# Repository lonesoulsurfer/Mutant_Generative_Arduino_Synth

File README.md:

# Mutant_Generative_Arduino_Synth

UPDATE: I have updated the Mutant code so it can be loaded using the most recent Mozzi Library.  You can find the code in the 'Mutant_Updated' file.  It works perfectly and there is no changes to the sounds etc.

 Meebleeps awesome Mutant Synth in modular format

First and foremost - I need to do a huge shoutout to MeeBleeps (https://github.com/Meebleeps/MeeBleeps-Mutant-Synth) who designed this amazing synth. I've designed a PCB and front panel to fit modular synths or you could use it as a stand alone synth if you wanted to.  You can power the synth used a voltage range from 9 to 12V's

You can find a step by step guide on my Instructables page on how to build your own - https://www.instructables.com/Mutant-Generative-Arduino-Synth/

I have also posted a video on my YouTube page - https://www.youtube.com/watch?v=L1Gzkz4_xpQ

The main goal with building this module is to create my own 'simple to build' modular synth. I wanted to keep everything as easy as possble with each module built with the following aims:

Can be powered by 9V (and 12V)
Easy to build with minimum components
Use Arduino to keep it simple (plus it helps to keep the components down and everything in tune)
Can fit into any modular synth Eurorck (include the ability to power the module via normal module power sources)
Has to sound great!
Lastly, it should be portable and be powered from a 9V battery

So what is the Mutant Synth? Well it's a generative synth based around a Arduino Nano and a handful of other components and produces a rich soundscape of sounds.

The synth voice is based around 2 saw oscillators that features:

Multiple tuning modes for the 2nd oscillator - off, detune, fifths & octaves up/down
Low pass filter with variable cutoff and resonance
Variable level ducking/sidechain effects
The display is a 8X8 LED matrix which allows you to visually see where each control level is at. This also includes a 16 step generative sequencer that mutates/evolves at defined rate depending on control inputs.

Variable sequence mutation probability & note-density
Sync input & output (Korg Volca compatible)
Note selection
Selectable scale quantization (Major, Minor, Pentatonic, Phrygian (GOA!), Octaves, Fifths)
16-step parameter-lock recording of synth parameters
Retrig (clone) button for different fills
Tap-tempo control

The Mozzi library used in the script is an older version which isn't a big deal but you will need to update IDE with an older version of Mozzie (1.1.2).  You can easily do this in IDE but if you are unsure how to do this then check out my Instruacable I published.

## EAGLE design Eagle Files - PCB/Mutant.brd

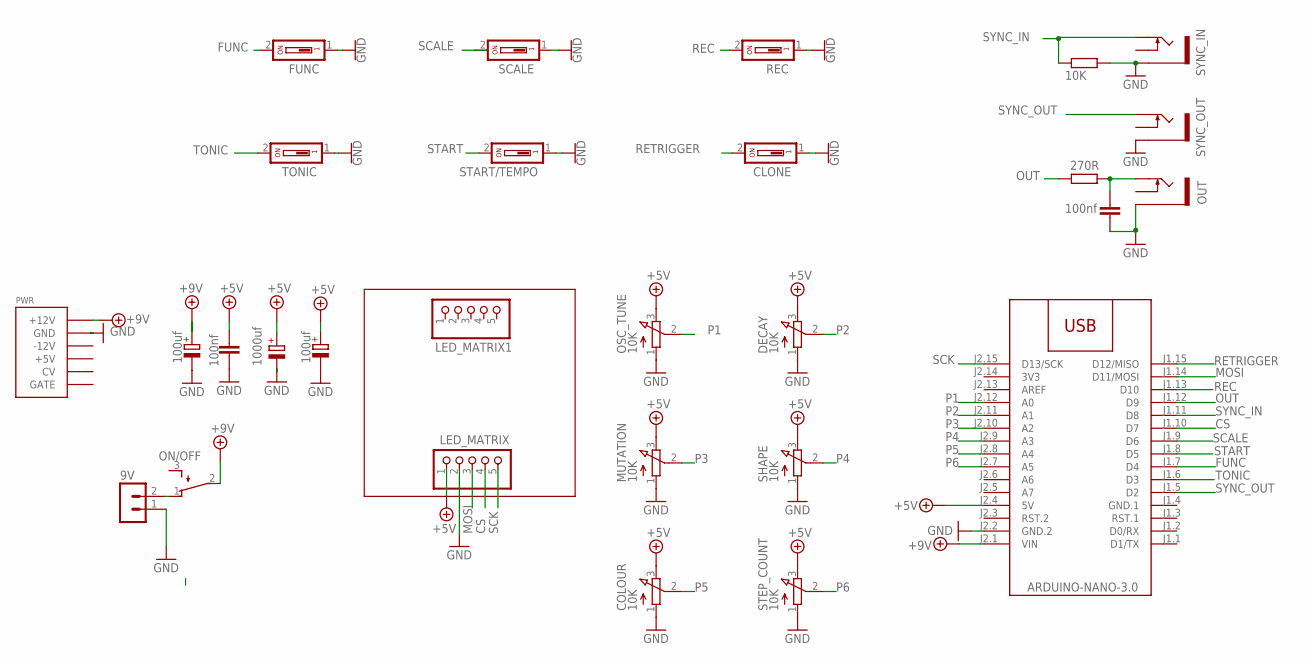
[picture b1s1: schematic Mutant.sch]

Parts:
9V: B2B-PH-K-S
C1, C4: 100nf; C050-024X044
C2, C3: 100uf; E2-5
C5: 1000uf; E2,5-6E
CLONE: DS01; DS-01
COLOUR: 10K; EVUFXL
DECAY: 10K; EVUFXL
FUNC: DS01; DS-01
LED_MATRIX, LED_MATRIX1: PINHD-1X5; 1X05
M1: ARDUINO-NANO-3.0
MUTATION: 10K; EVUFXL
ON/OFF: TL32PO; TL3XPO
OSC_TUNE: 10K; EVUFXL
OUT: THONKICONNNEW; WQP-PJ301M-12_JACK
PWR: POWER; POWER_16
R7: 10K; 0207/10
R8: 270R; 0207/10
REC: DS01; DS-01
SCALE: DS01; DS-01
SHAPE: 10K; EVUFXL
START/TEMPO: DS01; DS-01
STEP_COUNT: 10K; EVUFXL
SYNC_IN: THONKICONNNEW; WQP-PJ301M-12_JACK
SYNC_OUT: THONKICONNNEW; WQP-PJ301M-12_JACK
TONIC: DS01; DS-01

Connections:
3V3: M1.J2.14 (3V3)
+5V: C1.1, C2.+, C5.+, COLOUR.3 (E), DECAY.3 (E), LED_MATRIX.1, M1.J2.4 (5V), MUTATION.3 (E), OSC_TUNE.3 (E), SHAPE.3 (E), STEP_COUNT.3 (E)
+9V: C3.+, M1.J2.1 (VIN), ON/OFF.2, PWR.9 (+12V), PWR.10 (+12V)
CS: LED_MATRIX.4, M1.J1.10 (D7)
FUNC: FUNC.2, M1.J1.7 (D4)
GND: 9V.1, C1.2, C2.-, C3.-, C4.2, C5.-, CLONE.1, COLOUR.1 (A), DECAY.1 (A), FUNC.1, LED_MATRIX.2, M1.J2.2 (GND.2), MUTATION.1 (A), OSC_TUNE.1 (A), OUT.P$3_SLEEVE (SLEEVE), PWR.3 (GND), PWR.4 (GND), PWR.5 (GND), PWR.6 (GND), PWR.7 (GND), PWR.8 (GND), R7.2, REC.1, SCALE.1, SHAPE.1 (A), START/TEMPO.1, STEP_COUNT.1 (A), SYNC_IN.P$3_SLEEVE (SLEEVE), SYNC_OUT.P$3_SLEEVE (SLEEVE), TONIC.1
GND.1: M1.J1.4 (GND.1)
MOSI: LED_MATRIX.3, M1.J1.14 (D11/MOSI)
unnamed: 9V.2, ON/OFF.1 (O)
unnamed: C4.1, OUT.P$1_TIP (TIP), R8.2
OUT: M1.J1.12 (D9), R8.1
P1: M1.J2.12 (A0), OSC_TUNE.2 (S)
P2: DECAY.2 (S), M1.J2.11 (A1)
P3: M1.J2.10 (A2), MUTATION.2 (S)
P4: M1.J2.9 (A3), SHAPE.2 (S)
P5: COLOUR.2 (S), M1.J2.8 (A4)
P6: M1.J2.7 (A5), STEP_COUNT.2 (S)
REC: M1.J1.13 (D10), REC.2
RETRIGGER: CLONE.2, M1.J1.15 (D12/MISO)
SCALE: M1.J1.9 (D6), SCALE.2
SCK: LED_MATRIX.5, M1.J2.15 (D13/SCK)
START: M1.J1.8 (D5), START/TEMPO.2
SYNC_IN: M1.J1.11 (D8), R7.1, SYNC_IN.P$1_TIP (TIP)
SYNC_OUT: M1.J1.5 (D2), SYNC_OUT.P$1_TIP (TIP)
TONIC: M1.J1.6 (D3), TONIC.2

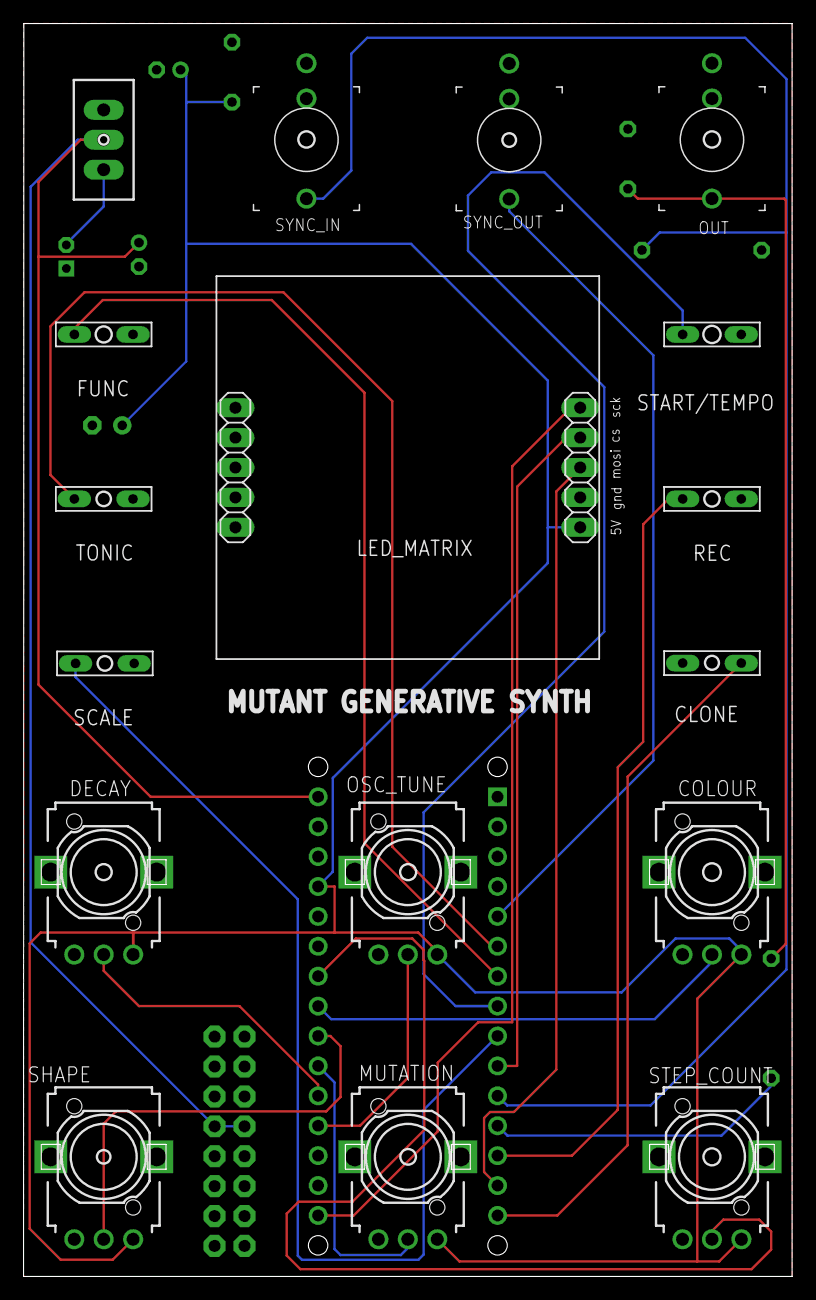
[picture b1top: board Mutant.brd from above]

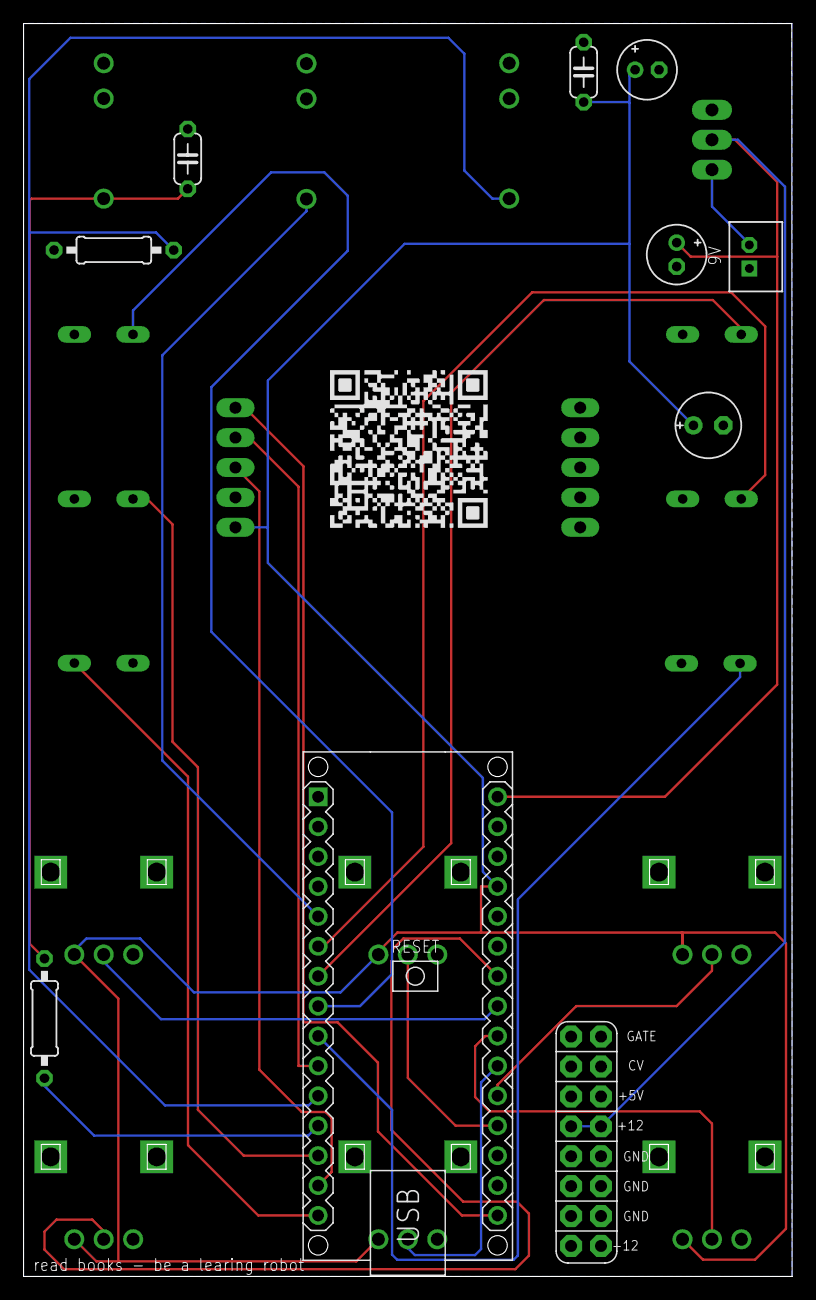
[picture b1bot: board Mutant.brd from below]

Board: 2 copper layers, 65.3 x 106.4 mm, 28 parts (10 on the bottom side), 23 nets.

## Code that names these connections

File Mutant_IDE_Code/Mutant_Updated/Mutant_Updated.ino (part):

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// #define CONTROL_RATE 256

// define the pins
#define PIN_SYNC_IN       8
#define PIN_SYNC_OUT      2
#define TIMER_SYNC_PULSE_OUTPUT_MILLIS 20

#define PIN_AUDIO_OUT     9
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#define BUTTON_INPUT_SCALE  2
#define BUTTON_INPUT_START  1
#define BUTTON_INPUT_REC    4  // D10 - Records pot movements (motion recording)
#define BUTTON_INPUT_RETRIG 5  // D12 - Clones/repeats note (retrigger function)


//#define MAX_OSCILLATOR_MODES 1
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  Serial.println(F("initialisePins()"));


  pinMode(PIN_SYNC_OUT, OUTPUT);
  pinMode(PIN_SYNC_IN, INPUT);          // sync is pulled down by external pulldown resistor
  pinMode(PIN_BUTTON0, INPUT_PULLUP);   // all other buttons are pulled up by internal pullup resistor
  pinMode(PIN_BUTTON1, INPUT_PULLUP);
  pinMode(PIN_BUTTON2, INPUT_PULLUP);
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  // check to see if the output sync pulse needs to be pulled low
  if (syncOutputTimer.ready())
  {
    digitalWrite(PIN_SYNC_OUT, LOW);
  }

  
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void outputSyncPulse()
{
  syncOutputTimer.start(TIMER_SYNC_PULSE_OUTPUT_MILLIS);
  digitalWrite(PIN_SYNC_OUT,  HIGH);
}


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 */
void updateSyncTrigger()
{
  iTrigger = digitalRead(PIN_SYNC_IN);   // read the sync pin

  if (iTrigger != iLastTrigger)
  {
    digitalWrite(PIN_SYNC_OUT, iTrigger);
    
    //trigger note on or off
    if (iTrigger == HIGH)
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
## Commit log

2024-12-09 Files
2025-06-22 Code updated - Define buttons for rec and retrig swapped
2025-11-28 README.md: public youtube url
    Linking to the public url for the video is a bit more helpful

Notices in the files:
Mutant_IDE_Code/Mutant_Updated/Mutant_Updated.ino:
(C) 2021 Meebleeps
parts and their libraries:
diy-modules: Released under the Creative Commons Attribution 4.0 International License: http://creativecommons.org/licenses/by/4.0
SparkFun-PowerSymbols: Licensing: Creative Commons ShareAlike 4.0 International - https://creativecommons.org/licenses/by-sa/4.0
